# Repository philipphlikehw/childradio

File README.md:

# childradio
An ESP32-based web radio designed specifically for small children.

The mechanics are highly robust, making it the only web radio capable of withstanding the daily life of a 1-year-old child.

## Key-Features:
- Robust Wooden Design: Built to endure rough handling.
- 2x3W Stereo Class-D Amplifier: Provides clear, powerful sound.
- Beautiful Cover: Enhances aesthetics and child-friendliness.
- RGB LED Lighting: Creates an attractive background glow behind the cover.
- Web Server for Parental Control: Parents can manage settings via a web interface.
- Child-Friendly Controls: Only volume adjustment and channel skipping are accessible to the child.
- USB-C Charging Port: Modern, convenient charging.
- Battery-Powered: Runs on a single 18650 cell, ensuring portability.

Please view this video for a demonstration
[Video](Mechanics/02_pics/VID_20241116_003110.mp4)

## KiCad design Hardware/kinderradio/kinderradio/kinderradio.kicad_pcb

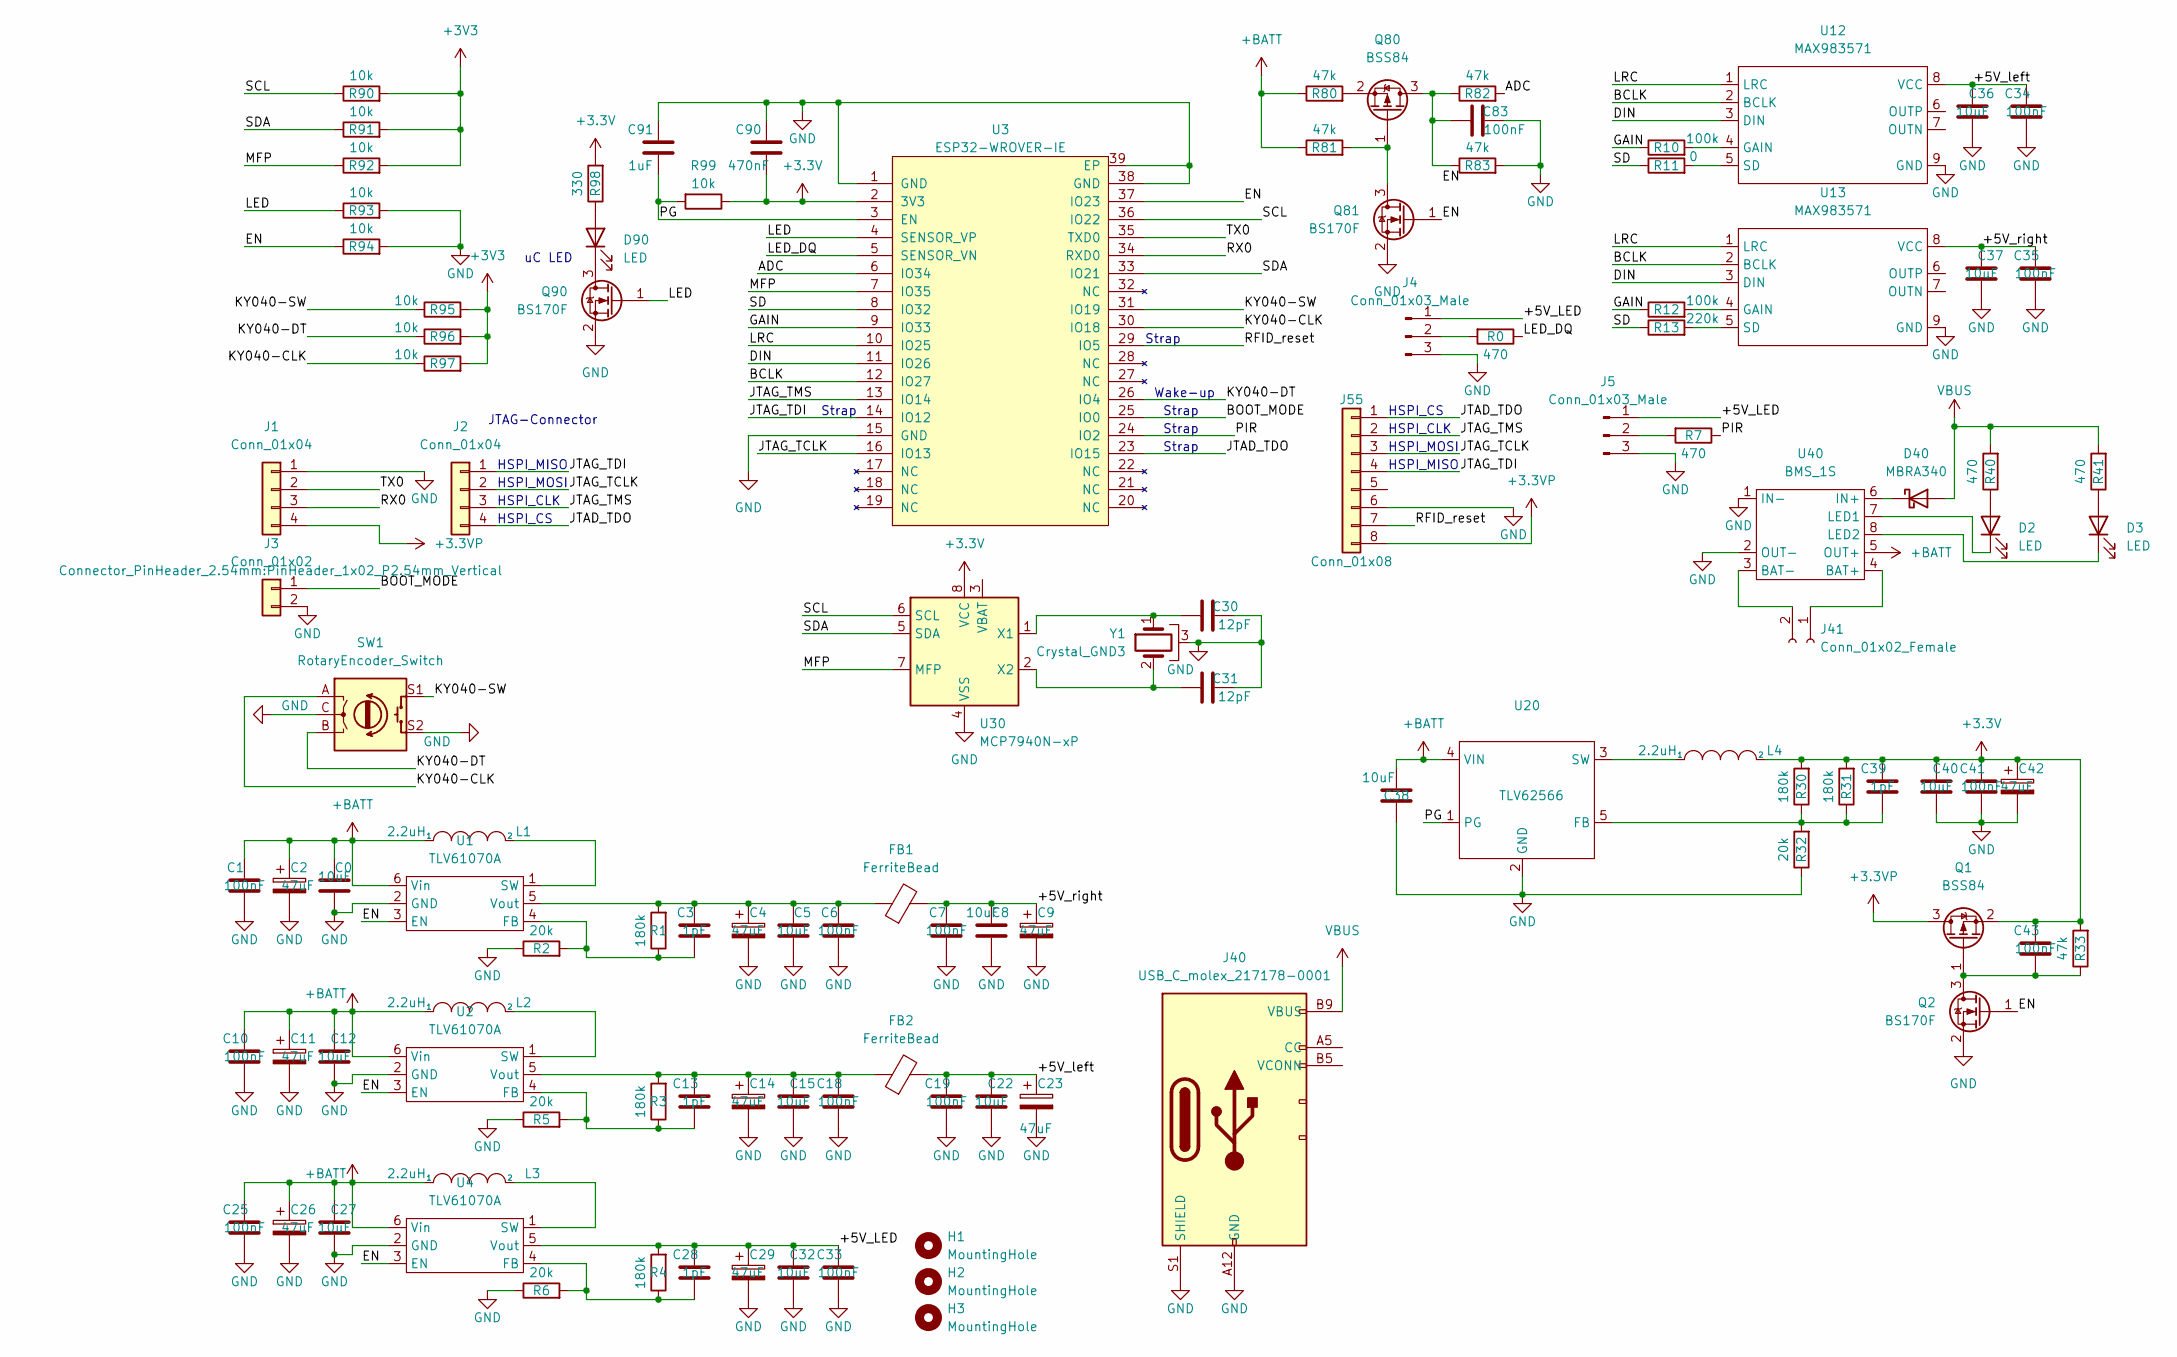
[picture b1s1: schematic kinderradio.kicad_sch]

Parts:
C0, C5, C8, C12, C15, C22, C27, C32, C36, C37, C38, C40: 10uF; R_1206_3216Metric
C1, C6, C7, C10, C18, C19, C25, C33, C34, C35, C41, C43, C83: 100nF; R_0805_2012Metric
C2, C4, C9, C11, C14, C23, C26, C29, C42: 47uF; CP_Elec_6.3x5.2
C3, C13, C28, C39: 1pF; R_0805_2012Metric
C30, C31: 12pF; R_0805_2012Metric
C90: 470nF; R_0805_2012Metric
C91: 1uF; R_0805_2012Metric
D2, D3, D90: LED; LED_D5.0mm
D40: MBRA340; D_SMA
FB1, FB2: FerriteBead; L_0805_2012Metric
H1, H2, H3: MountingHole; MountingHole_3.2mm_M3
J1, J2: Conn_01x04; PinHeader_1x04_P2.54mm_Vertical
J3: Conn_01x02; PinHeader_1x02_P2.54mm_Vertical
J4, J5: Conn_01x03_Male; PinHeader_1x03_P2.54mm_Vertical
J40: USB_C_molex_217178-0001; 217178-0001
J41: Conn_01x02_Female; Connector
J55: Conn_01x08; PinHeader_1x08_P2.54mm_Vertical
L1, L2, L3, L4: 2.2uH; L_1008_2520Metric; part TFM252012ALVA2R2MTAA
Q1, Q80: BSS84; SOT-23
Q2, Q81, Q90: BS170F; SOT-23
R0, R7, R40, R41: 470; R_0805_2012Metric
R1, R3, R4, R30, R31: 180k; R_0805_2012Metric
R2, R5, R6, R32: 20k; R_0805_2012Metric
R10, R12: 100k; R_0805_2012Metric
R11: 0; R_0805_2012Metric
R13: 220k; R_0805_2012Metric
R33, R80, R81, R82, R83: 47k; R_0805_2012Metric
R90, R91, R92, R93, R94, R95, R96, R97, R99: 10k; R_0805_2012Metric
R98: 330; R_0805_2012Metric
SW1: RotaryEncoder_Switch; RotaryEncoder_Alps_EC11E-Switch_Vertical_H20mm
U1, U2, U4: TLV61070A; SOT-23-6
U3: ESP32-WROVER-IE
U12, U13: MAX983571; max98357a
U20: TLV62566; SOT-23-5
U30: MCP7940N-xP; SOIC-8_3.9x4.9mm_P1.27mm
U40: BMS_1S
Y1: Crystal_GND3; Crystal_DS15_D1.5mm_L5.0mm_Horizontal_1EP_style2

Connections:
+3.3VP: J1.4, J55.8, Q1.3 (D)
+BATT: C0.2, C1.1, C2.1, C10.1, C11.1, C12.2, C25.1, C26.1, C27.2, C38.2, L1.1, L2.1, L3.1, R80.1, R81.1, U1.6 (Vin), U2.6 (Vin), U4.6 (Vin), U20.4 (VIN), U40.5 (OUT+)
/+5V_LED: C28.1, C29.1, C32.2, C33.1, J4.1, J5.1, R4.2, U4.5 (Vout)
/+5V_left: C19.1, C22.2, C23.1, C34.1, C36.2, FB2.2, U12.8 (VCC)
/+5V_right: C7.1, C8.2, C9.1, C35.1, C37.2, FB1.2, U13.8 (VCC)
/ADC: R82.2, U3.6 (IO34)
/BCLK: U3.12 (IO27), U12.2 (BCLK), U13.2 (BCLK)
/BOOT_MODE: J3.1, U3.25 (IO0)
/DIN: U3.11 (IO26), U12.3 (DIN), U13.3 (DIN)
/EN: Q2.1 (G), Q81.1 (G), R94.1, U1.3 (EN), U2.3 (EN), U3.37 (IO23), U4.3 (EN)
/GAIN: R10.1, R12.1, U3.9 (IO33)
/JTAD_TDO: J2.4, J55.1, U3.23 (IO15)
/JTAG_TCLK: J2.2, J55.3, U3.16 (IO13)
/JTAG_TDI: J2.1, J55.4, U3.14 (IO12)
/JTAG_TMS: J2.3, J55.2, U3.13 (IO14)
/KY040-CLK: R97.1, SW1.A, U3.30 (IO18)
/KY040-DT: R96.1, SW1.B, U3.26 (IO4)
/KY040-SW: R95.1, SW1.S1, U3.31 (IO19)
/LED: Q90.1 (G), R93.1, U3.4 (SENSOR_VP)
/LED_DQ: R0.1, U3.5 (SENSOR_VN)
/LRC: U3.10 (IO25), U12.1 (LRC), U13.1 (LRC)
/MFP: R92.1, U3.7 (IO35), U30.7 (MFP)
/PG: C91.1, R99.2, U3.3 (EN), U20.1 (PG)
/PIR: R7.1, U3.24 (IO2)
/RFID_reset: J55.7, U3.29 (IO5)
/RX0: J1.3, U3.34 (RXD0)
/SCL: R90.1, U3.36 (IO22), U30.6 (SCL)
/SD: R11.1, R13.1, U3.8 (IO32)
/SDA: R91.1, U3.33 (IO21), U30.5 (SDA)
/TX0: J1.2, U3.35 (TXD0)
GND: C0.1, C1.2, C2.2, C4.2, C5.1, C6.2, C7.2, C8.1, C9.2, C10.2, C11.2, C12.1, C14.2, C15.1, C18.2, C19.2, C22.1, C23.2, C25.2, C26.2, C27.1, C29.2, C30.1, C31.1, C32.1, C33.2, C34.2, C35.2, C36.1, C37.1, C38.1, C40.1, C41.2, C42.2, C83.1, C90.2, C91.2, J1.1, J3.2, J4.3, J5.3, J40.A12 (GND), J40.B12 (GND), J40.S1 (SHIELD), J40.S2 (SHIELD), J55.6, Q2.2 (S), Q81.2 (S), Q90.2 (S), R2.1, R5.1, R6.1, R32.1, R83.2, R93.2, R94.2, SW1.C, SW1.S2, U1.2 (GND), U2.2 (GND), U3.1 (GND), U3.15 (GND), U3.38 (GND), U3.39 (EP), U4.2 (GND), U12.9 (GND), U13.9 (GND), U20.2 (GND), U30.4 (VSS), U40.1 (IN-), U40.2 (OUT-), Y1.3
unnamed: C3.1, C4.1, C5.2, C6.1, FB1.1, R1.2, U1.5 (Vout)
unnamed: C3.2, R1.1, R2.2, U1.4 (FB)
unnamed: C13.1, C14.1, C15.2, C18.1, FB2.1, R3.2, U2.5 (Vout)
unnamed: C13.2, R3.1, R5.2, U2.4 (FB)
unnamed: C28.2, R4.1, R6.2, U4.4 (FB)
unnamed: C30.2, U30.1 (X1), Y1.1
unnamed: C31.2, U30.2 (X2), Y1.2
unnamed: C39.2, R30.1, R31.1, R32.2, U20.5 (FB)
unnamed: C83.2, Q80.3 (D), R82.1, R83.1
unnamed: D2.1 (K), U40.7 (LED1)
unnamed: D2.2 (A), R40.1
unnamed: D3.1 (K), U40.8 (LED2)
unnamed: D3.2 (A), R41.1
unnamed: D40.1 (K), U40.6 (IN+)
unnamed: D90.1 (K), Q90.3 (D)
unnamed: D90.2 (A), R98.1
unnamed: J4.2, R0.2
unnamed: J5.2, R7.2
unnamed: L1.2, U1.1 (SW)
unnamed: L2.2, U2.1 (SW)
unnamed: L3.2, U4.1 (SW)
unnamed: L4.1, U20.3 (SW)
unnamed: C43.2, Q1.1 (G), Q2.3 (D), R33.1
unnamed: R10.2, U12.4 (GAIN)
unnamed: R11.2, U12.5 (SD)
unnamed: R12.2, U13.4 (GAIN)
unnamed: R13.2, U13.5 (SD)
unnamed: Q80.2 (S), R80.2
unnamed: Q80.1 (G), Q81.3 (D), R81.2
unnamed: J41.2, U40.3 (BAT-)
unnamed: J41.1, U40.4 (BAT+)
VBUS: D40.2 (A), J40.A9 (VBUS), J40.B9 (VBUS), R40.2, R41.2

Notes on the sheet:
uC LED
HSPI_MOSI
Strap
HSPI_CS
HSPI_CLK
Wake-up
HSPI_MISO
JTAG-Connector

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
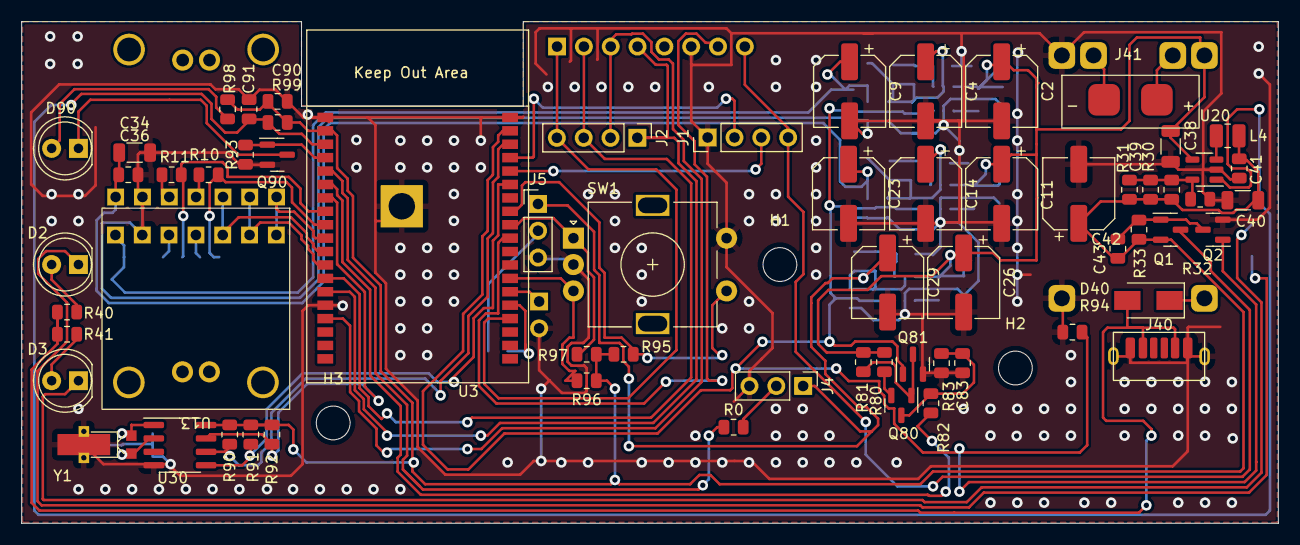
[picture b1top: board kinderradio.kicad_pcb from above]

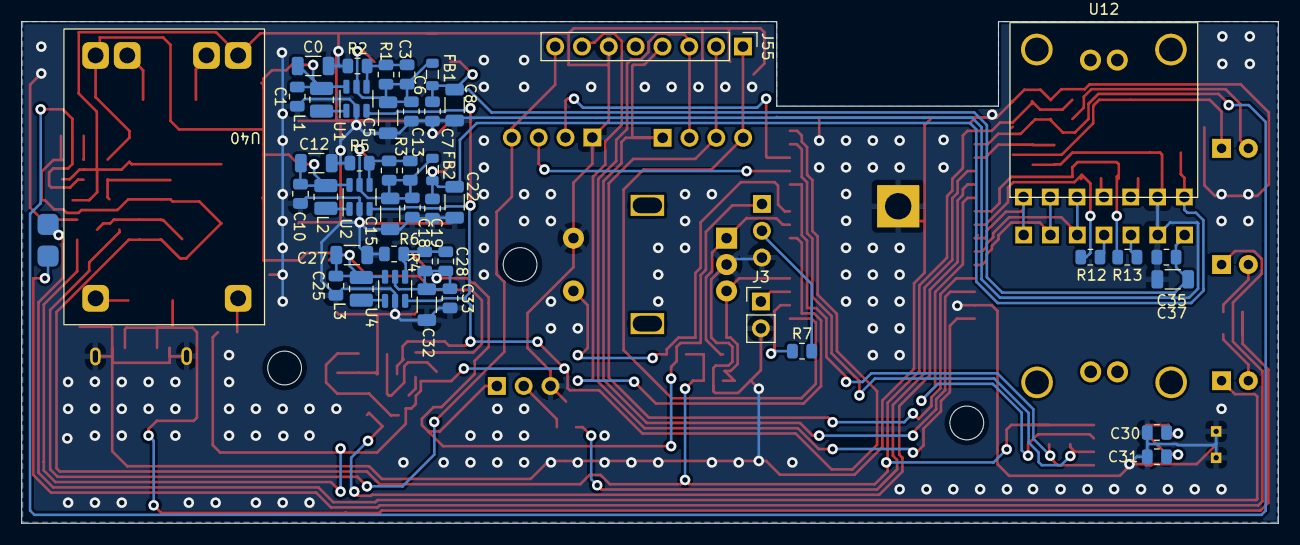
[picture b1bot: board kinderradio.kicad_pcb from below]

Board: 2 copper layers, 119.0 x 47.5 mm, 111 parts (44 on the bottom side), 64 nets.

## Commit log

2023-01-06 Initial HW Commit
2024-11-15 second run doko 1
2024-11-15 second run doko 2
2024-11-15 second run doko 3
2025-12-16 update new Software Dec25, KinderradioV2, first HW ideas
